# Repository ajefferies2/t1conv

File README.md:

# t1conv

Current Progress: Finished schematics, workinf on layout
100BASE-T1 ↔ 100BASE-TX media converter + dual CAN FD/USB adapter on one
board.

## Features

- Wire-speed T1↔TX conversion, PHY-to-PHY (DP83TC811 ↔ DP83822 over RGMII).
  No MAC, no firmware in the data path, converts with the MCU in reset.
- Two independent CAN FD channels over USB, using the gs_usb protocol:
  works out of the box with SocketCAN, python-can, and SavvyCAN.
- Software-switchable termination on each CAN channel (PhotoMOS; for example,
  `ip link set can0 type can termination 120`).
- Software-selectable T1 master/slave: FET on the strap pin, resampled by
  PHY reset. Boards are identical; role is a console command.
- Powered and flashed over USB-C. Blank MCU enumerates in DFU; BOOT button
  for recovery; SWD pads as last resort.

## Info

- Transformerless T1 MDI: TI-validated CMC, CM termination matched to that
  specific choke, 2 kV coupling network, 100 Ω differential on both MDI sides.
- Back-to-back RGMII delay budget: 25 MHz SDR at 100M, TX+RX internal delay
  strapped in the T1 PHY, strap tables derived from SNLA292/SNLU231.

## Schematics

The images below are exported from the current KiCad hierarchy.

### Top level

### Power

### MCU

### Dual CAN FD

### 100BASE-T1 PHY

### 100BASE-TX Ethernet PHY

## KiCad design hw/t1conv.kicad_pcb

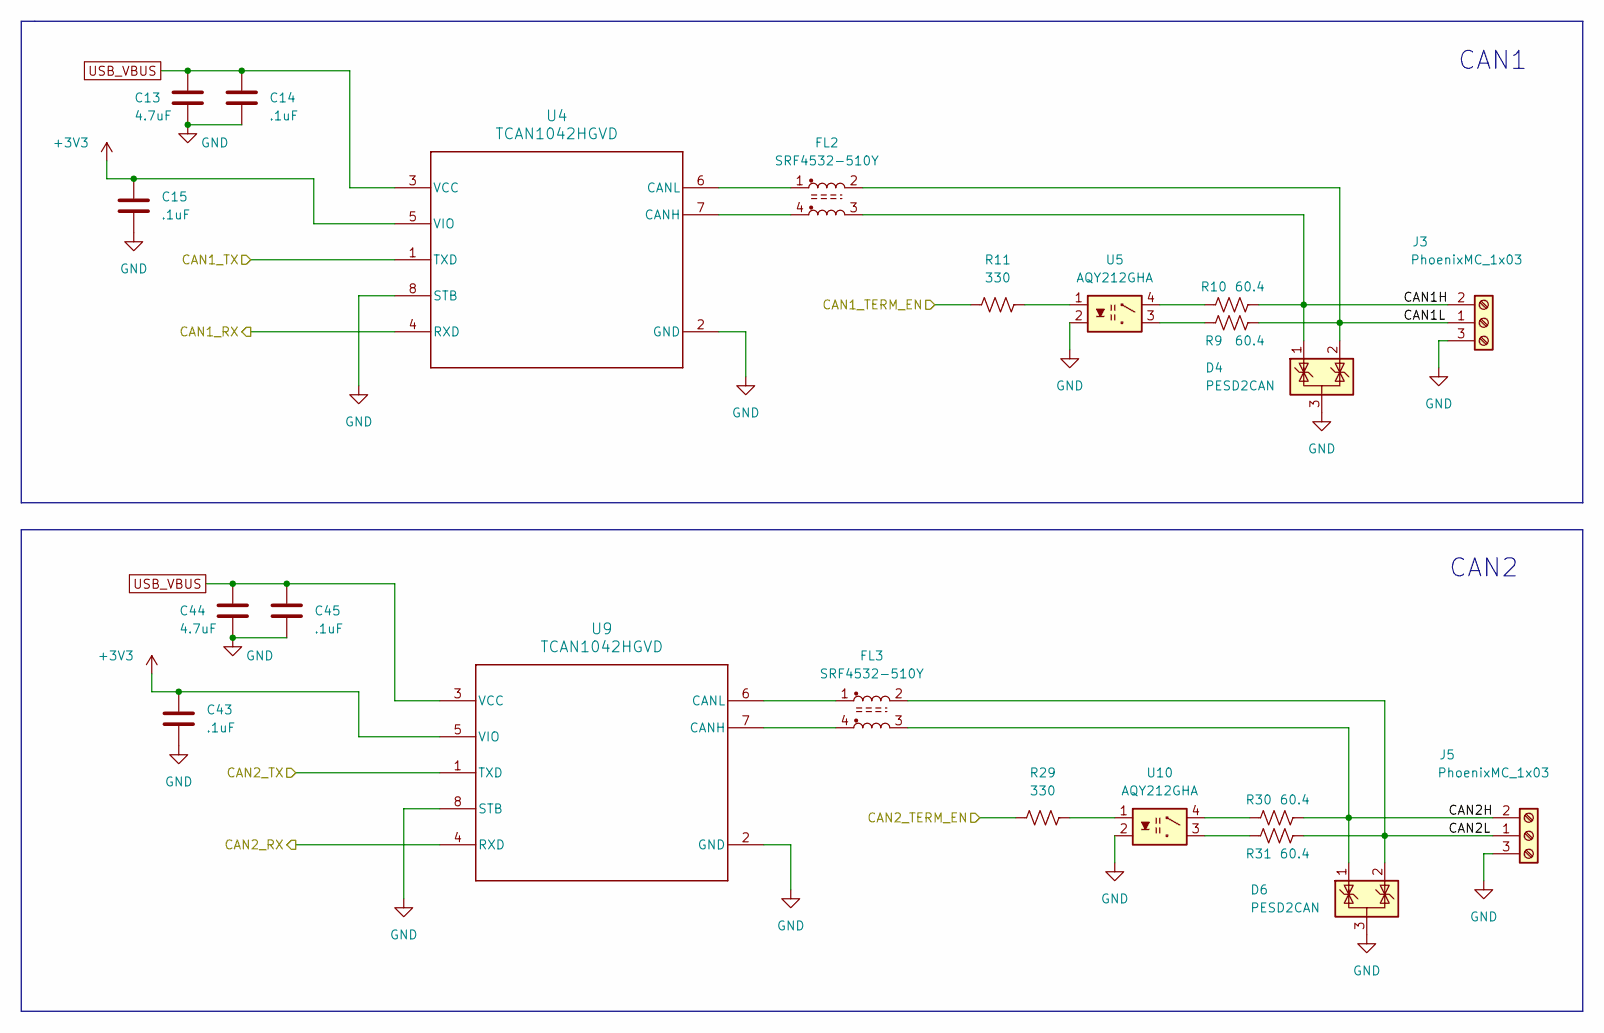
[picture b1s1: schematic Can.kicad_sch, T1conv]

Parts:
C13, C44: 4.7uF; C_0603_1608Metric
C14, C15, C43, C45: .1uF; C_0603_1608Metric
D4, D6: PESD2CAN; SOT-23; MPN PESD2CAN,215; DigiKey 1727-3891-1-ND
FL2, FL3: SRF4532-510Y; SRF4532; MPN SRF4532-510Y; LCSC C2651134
J3, J5: PhoenixMC_1x03; PhoenixContact_MC_1,5_3-G-3.5_1x03_P3.50mm_Horizontal; MPN 1803581
R9, R10, R30, R31: 60.4; R_0603_1608Metric
R11, R29: 330; R_0603_1608Metric
U4, U9: TCAN1042HGVD; TCAN1042_VSON8; MPN TCAN1042HGVD; DigiKey 296-TCAN1042HGVDR-ND
U5, U10: AQY212GHA; MPN AQY212GHAX; DigiKey 255-6063-1-ND

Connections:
+3V3: C15.1, C43.1, U4.5 (VIO), U9.5 (VIO); also elsewhere on the board
/CanSheet/CAN1H: D4.1 (K), FL2.3, J3.2, R10.2
/CanSheet/CAN1L: D4.2 (K), FL2.2, J3.1, R9.2
/CanSheet/CAN1_RX: U4.4 (RXD); also elsewhere on the board
/CanSheet/CAN1_TERM_EN: R11.2; also elsewhere on the board
/CanSheet/CAN1_TX: U4.1 (TXD); also elsewhere on the board
/CanSheet/CAN2H: D6.1 (K), FL3.3, J5.2, R30.2
/CanSheet/CAN2L: D6.2 (K), FL3.2, J5.1, R31.2
/CanSheet/CAN2_RX: U9.4 (RXD); also elsewhere on the board
/CanSheet/CAN2_TERM_EN: R29.2; also elsewhere on the board
/CanSheet/CAN2_TX: U9.1 (TXD); also elsewhere on the board
GND: C13.2, C14.2, C15.2, C43.2, C44.2, C45.2, D4.3 (A), D6.3 (A), J3.3, J5.3, U4.2 (GND), U4.8 (STB), U5.2, U9.2 (GND), U9.8 (STB), U10.2; also elsewhere on the board
unnamed: R9.1, U5.3
unnamed: R10.1, U5.4
unnamed: R11.1, U5.1
unnamed: R29.1, U10.1
unnamed: R30.1, U10.4
unnamed: R31.1, U10.3
unnamed: FL2.4, U4.7 (CANH)
unnamed: FL2.1, U4.6 (CANL)
unnamed: FL3.4, U9.7 (CANH)
unnamed: FL3.1, U9.6 (CANL)
USB_VBUS: C13.1, C14.1, C44.1, C45.1, U4.3 (VCC), U9.3 (VCC); also elsewhere on the board

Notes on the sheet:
CAN2
CAN1

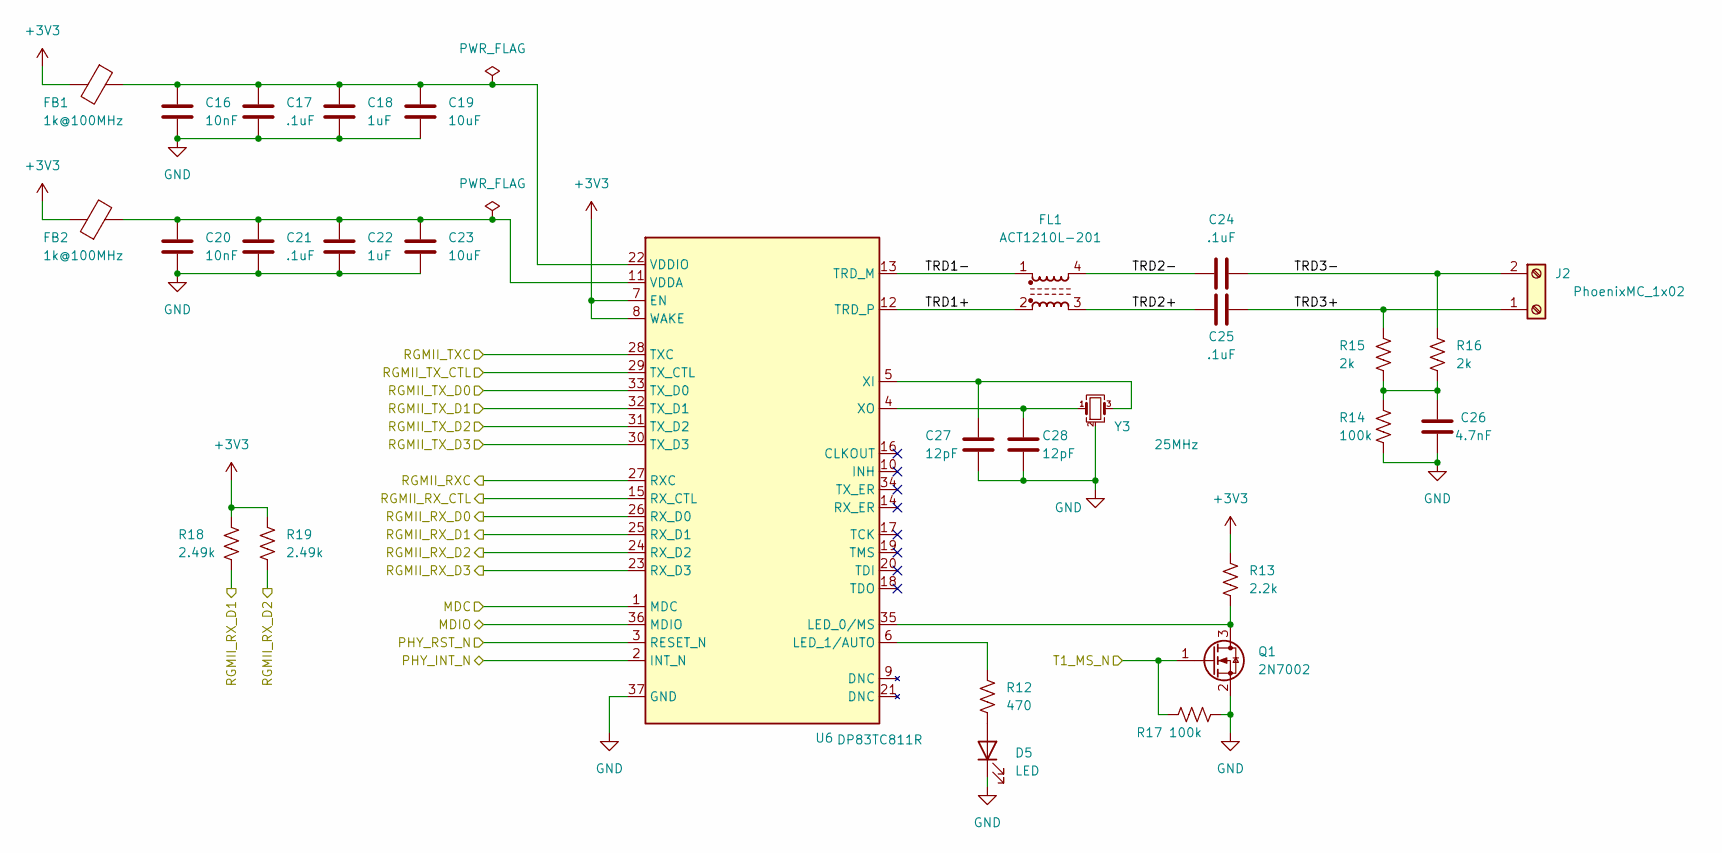
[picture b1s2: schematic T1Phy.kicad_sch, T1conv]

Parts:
C16, C20: 10nF; C_0603_1608Metric
C17, C21, C24, C25: .1uF; C_0603_1608Metric
C18, C22: 1uF; C_0603_1608Metric
C19, C23: 10uF; C_0603_1608Metric
C26: 4.7nF; C_0603_1608Metric
C27, C28: 12pF; C_0603_1608Metric
D5: LED; LED_0603_1608Metric
FB1, FB2: 1k@100MHz; R_0805_2012Metric; MPN house-brand basic tier - pick at sweep 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
FL1: ACT1210L-201; ACT1210L_3225; MPN ACT1210L-201-2P-TL00; DigiKey 445-ACT1210L-201-2P-TL00CT-ND
J2: PhoenixMC_1x02; PhoenixContact_MC_1,5_2-G-3.5_1x02_P3.50mm_Horizontal; MPN 1803578
Q1: 2N7002; SOT-23; MPN 2N7002; LCSC C8545
R12: 470; R_0603_1608Metric
R13: 2.2k; R_0603_1608Metric
R14, R17: 100k; R_0603_1608Metric
R15, R16: 2k; R_0603_1608Metric
R18, R19: 2.49k; R_0603_1608Metric
U6: DP83TC811R; DP83TC811R_RND0036A; MPN DP83TC811RWRNDRQ1; DigiKey 296-DP83TC811RWRNDRQ1-ND
Y3: 25MHz; Crystal_SMD_3225-4Pin_3.2x2.5mm

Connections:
+3V3: FB1.2, FB2.1, R13.1, R18.1, R19.1, U6.7 (EN), U6.8 (WAKE); also elsewhere on the board
/Ethernet/MDC: U6.1 (MDC); also elsewhere on the board
/Ethernet/MDIO: U6.36 (MDIO); also elsewhere on the board
/Ethernet/PHY_INT_N: U6.2 (INT_N); also elsewhere on the board
/Ethernet/PHY_RST_N: U6.3 (RESET_N); also elsewhere on the board
/Ethernet/RGMII_RXC: U6.27 (RXC); also elsewhere on the board
/Ethernet/RGMII_RX_CTL: U6.15 (RX_CTL); also elsewhere on the board
/Ethernet/RGMII_RX_D0: U6.26 (RX_D0); also elsewhere on the board
/Ethernet/RGMII_RX_D1: R18.2, U6.25 (RX_D1); also elsewhere on the board
/Ethernet/RGMII_RX_D2: R19.2, U6.24 (RX_D2); also elsewhere on the board
/Ethernet/RGMII_RX_D3: U6.23 (RX_D3); also elsewhere on the board
/Ethernet/RGMII_TXC: U6.28 (TXC); also elsewhere on the board
/Ethernet/RGMII_TX_CTL: U6.29 (TX_CTL); also elsewhere on the board
/Ethernet/RGMII_TX_D0: U6.33 (TX_D0); also elsewhere on the board
/Ethernet/RGMII_TX_D1: U6.32 (TX_D1); also elsewhere on the board
/Ethernet/RGMII_TX_D2: U6.31 (TX_D2); also elsewhere on the board
/Ethernet/RGMII_TX_D3: U6.30 (TX_D3); also elsewhere on the board
/MCU/T1_MS_N: Q1.1 (G), R17.1; also elsewhere on the board
/T1Phy/TRD1+: FL1.2, U6.12 (TRD_P)
/T1Phy/TRD1-: FL1.1, U6.13 (TRD_M)
/T1Phy/TRD2+: C25.2, FL1.3
/T1Phy/TRD2-: C24.1, FL1.4
/T1Phy/TRD3+: C25.1, J2.1, R15.1
/T1Phy/TRD3-: C24.2, J2.2, R16.1
GND: C16.2, C17.2, C18.2, C19.2, C20.2, C21.2, C22.2, C23.2, C26.2, C27.2, C28.2, D5.1 (K), Q1.2 (S), R14.2, R17.2, U6.37 (GND), Y3.2 (G), Y3.4 (G); also elsewhere on the board
unnamed: C26.1, R14.1, R15.2, R16.2
unnamed: D5.2 (A), R12.2
unnamed: Q1.3 (D), R13.2, U6.35 (LED_0/MS)
unnamed: R12.1, U6.6 (LED_1/AUTO)
unnamed: C20.1, C21.1, C22.1, C23.1, FB2.2, U6.11 (VDDA)
unnamed: C16.1, C17.1, C18.1, C19.1, FB1.1, U6.22 (VDDIO)
unnamed: C27.1, U6.5 (XI), Y3.3
unnamed: C28.1, U6.4 (XO), Y3.1

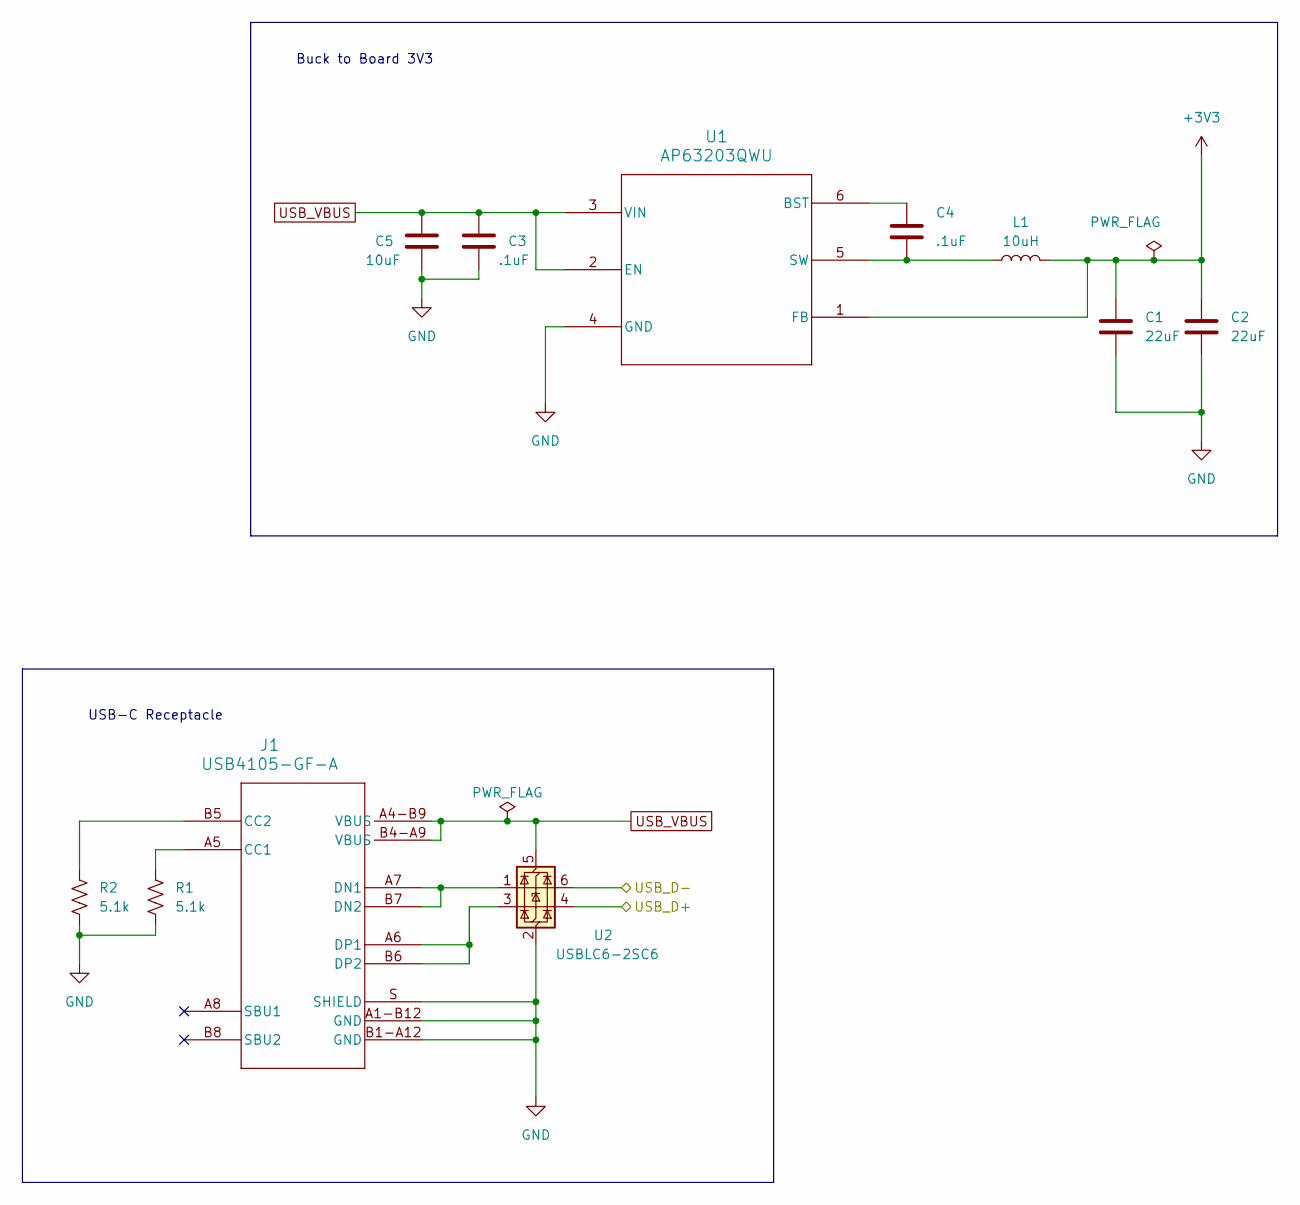
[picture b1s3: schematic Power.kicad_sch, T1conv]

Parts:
C1, C2: 22uF; C_0603_1608Metric
C3, C4: .1uF; C_0603_1608Metric
C5: 10uF; C_0603_1608Metric
J1: USB4105-GF-A; MPN USB4105-GF-A; DigiKey 2073-USB4105-GF-ACT-ND
L1: 10uH; SWPA5040
R1, R2: 5.1k; R_0603_1608Metric
U1: AP63203QWU; AP63203_TSOT26; MPN AP63203QWU-7; DigiKey AP63203QWU-7DICT-ND
U2: USBLC6-2SC6; SOT-23-6; MPN USBLC6-2SC6; DigiKey 497-5235-1-ND

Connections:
+3V3: C1.1, C2.1, L1.2, U1.1 (FB); also elsewhere on the board
/MCU/USB_D+: U2.4 (I/O2); also elsewhere on the board
/MCU/USB_D-: U2.6 (I/O1); also elsewhere on the board
GND: C1.2, C2.2, C3.2, C5.2, J1.A1-B12 (GND), J1.B1-A12 (GND), J1.S (SHIELD), R1.2, R2.2, U1.4 (GND), U2.2 (GND); also elsewhere on the board
unnamed: J1.A5 (CC1), R1.1
unnamed: J1.B5 (CC2), R2.1
unnamed: J1.A7 (DN1), J1.B7 (DN2), U2.1 (I/O1)
unnamed: J1.A6 (DP1), J1.B6 (DP2), U2.3 (I/O2)
unnamed: C4.1, U1.6 (BST)
unnamed: C4.2, L1.1, U1.5 (SW)
USB_VBUS: C3.1, C5.1, J1.A4-B9 (VBUS), J1.B4-A9 (VBUS), U1.2 (EN), U1.3 (VIN), U2.5 (VBUS); also elsewhere on the board

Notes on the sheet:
USB-C Receptacle
Buck to Board 3V3

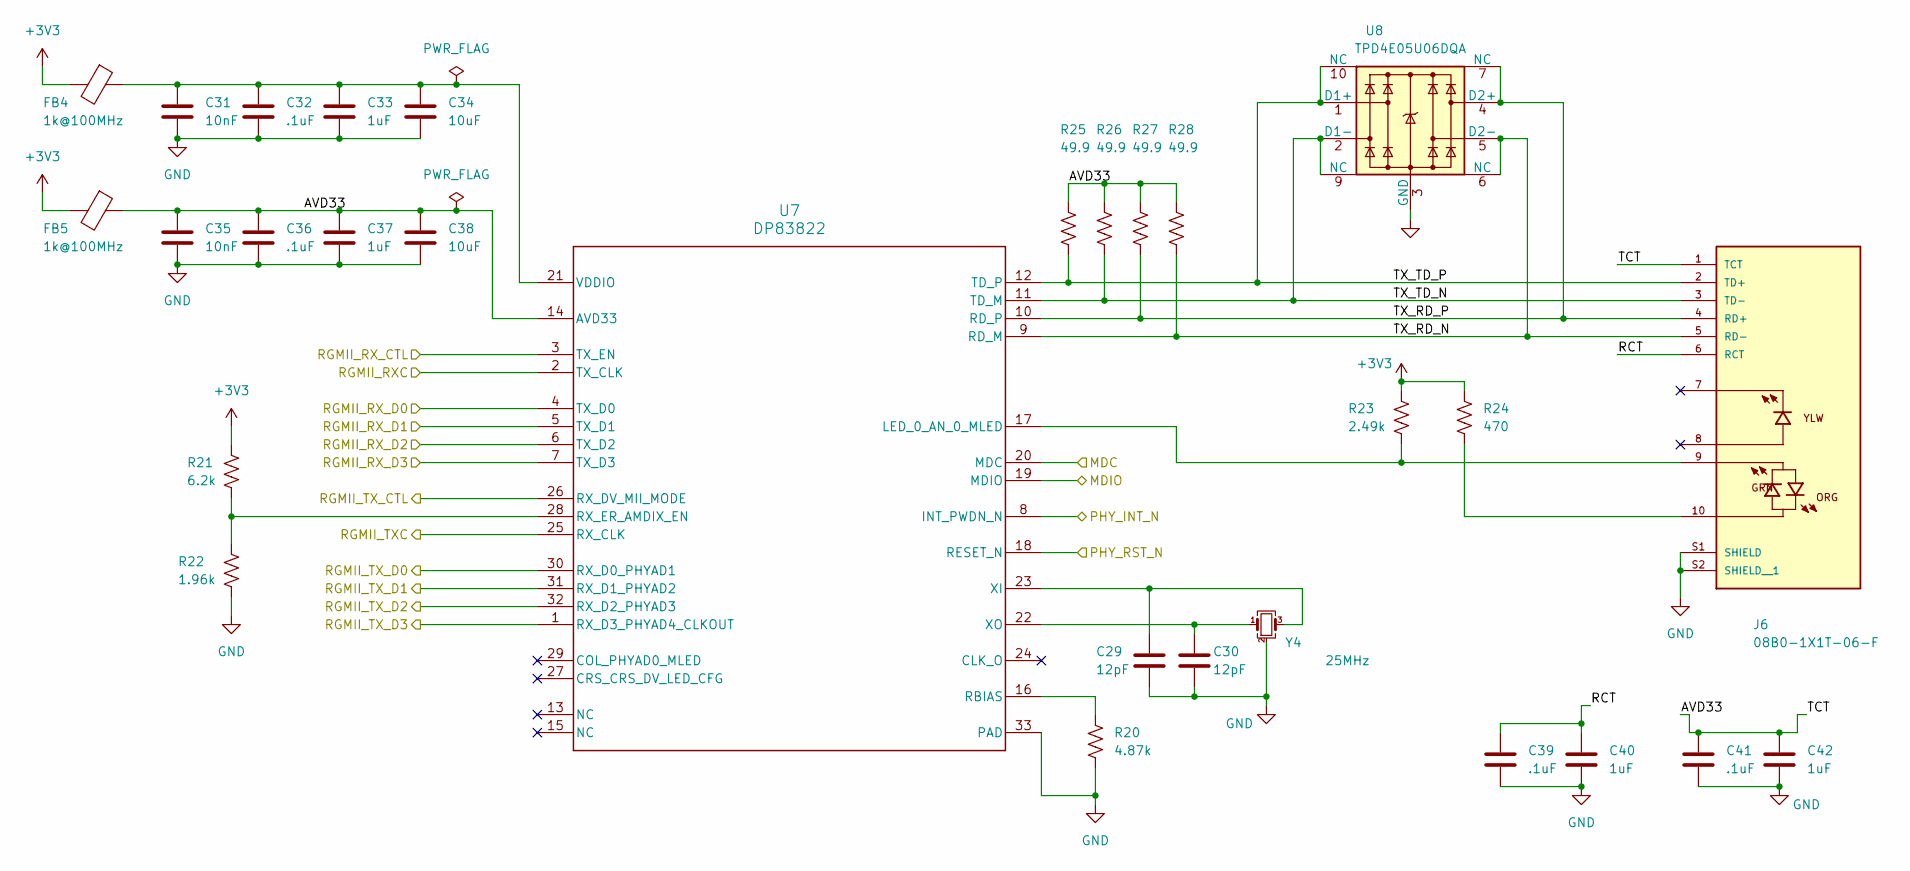
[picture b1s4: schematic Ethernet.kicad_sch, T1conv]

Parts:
C29, C30: 12pF; C_0603_1608Metric
C31, C35: 10nF; C_0603_1608Metric
C32, C36, C39, C41: .1uF; C_0603_1608Metric
C33, C37, C40, C42: 1uF; C_0603_1608Metric
C34, C38: 10uF; C_0603_1608Metric
FB4, FB5: 1k@100MHz; R_0805_2012Metric; MPN house-brand basic tier - pick at sweep 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
J6: 08B0-1X1T-06-F; MPN 08B0-1X1T-06-F; DigiKey 507-1445-ND
R20: 4.87k; R_0603_1608Metric
R21: 6.2k; R_0603_1608Metric
R22: 1.96k; R_0603_1608Metric
R23: 2.49k; R_0603_1608Metric
R24: 470; R_0603_1608Metric
R25, R26, R27, R28: 49.9; R_0603_1608Metric
U7: DP83822; DP83822_RHB0032B; MPN DP83822IRHBR; DigiKey 296-DP83822IRHBRCT-ND
U8: TPD4E05U06DQA; TPD4E05U06_DQA0010A; MPN TPD4E05U06DQAR; DigiKey 296-35765-1-ND
Y4: 25MHz; Crystal_SMD_3225-4Pin_3.2x2.5mm

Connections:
+3V3: FB4.2, FB5.2, R21.1, R23.1, R24.1; also elsewhere on the board
/Ethernet/AVD33: C35.1, C36.1, C37.1, C38.1, C41.1, C42.1, FB5.1, J6.1 (TCT), R25.1, R26.1, R27.1, R28.1, U7.14 (AVD33)
/Ethernet/MDC: U7.20 (MDC); also elsewhere on the board
/Ethernet/MDIO: U7.19 (MDIO); also elsewhere on the board
/Ethernet/PHY_INT_N: U7.8 (INT_PWDN_N); also elsewhere on the board
/Ethernet/PHY_RST_N: U7.18 (RESET_N); also elsewhere on the board
/Ethernet/RCT: C39.1, C40.1, J6.6 (RCT)
/Ethernet/RGMII_RXC: U7.2 (TX_CLK); also elsewhere on the board
/Ethernet/RGMII_RX_CTL: U7.3 (TX_EN); also elsewhere on the board
/Ethernet/RGMII_RX_D0: U7.4 (TX_D0); also elsewhere on the board
/Ethernet/RGMII_RX_D1: U7.5 (TX_D1); also elsewhere on the board
/Ethernet/RGMII_RX_D2: U7.6 (TX_D2); also elsewhere on the board
/Ethernet/RGMII_RX_D3: U7.7 (TX_D3); also elsewhere on the board
/Ethernet/RGMII_TXC: U7.25 (RX_CLK); also elsewhere on the board
/Ethernet/RGMII_TX_CTL: U7.26 (RX_DV_MII_MODE); also elsewhere on the board
/Ethernet/RGMII_TX_D0: U7.30 (RX_D0_PHYAD1); also elsewhere on the board
/Ethernet/RGMII_TX_D1: U7.31 (RX_D1_PHYAD2); also elsewhere on the board
/Ethernet/RGMII_TX_D2: U7.32 (RX_D2_PHYAD3); also elsewhere on the board
/Ethernet/RGMII_TX_D3: U7.1 (RX_D3_PHYAD4_CLKOUT); also elsewhere on the board
/Ethernet/TX_RD_N: J6.5 (RD-), R28.2, U7.9 (RD_M), U8.5 (D2-), U8.6 (NC)
/Ethernet/TX_RD_P: J6.4 (RD+), R27.2, U7.10 (RD_P), U8.4 (D2+), U8.7 (NC)
/Ethernet/TX_TD_N: J6.3 (TD-), R26.2, U7.11 (TD_M), U8.2 (D1-), U8.9 (NC)
/Ethernet/TX_TD_P: J6.2 (TD+), R25.2, U7.12 (TD_P), U8.1 (D1+), U8.10 (NC)
GND: C29.2, C30.2, C31.2, C32.2, C33.2, C34.2, C35.2, C36.2, C37.2, C38.2, C39.2, C40.2, C41.2, C42.2, J6.S1 (SHIELD), J6.S2 (SHIELD__1), R20.2, R22.2, U7.33 (PAD), U8.3 (GND), U8.8 (GND), Y4.2 (G), Y4.4 (G); also elsewhere on the board
unnamed: J6.10, R24.2
unnamed: J6.9, R23.2, U7.17 (LED_0_AN_0_MLED)
unnamed: R20.1, U7.16 (RBIAS)
unnamed: R21.2, R22.1, U7.28 (RX_ER_AMDIX_EN)
unnamed: C31.1, C32.1, C33.1, C34.1, FB4.1, U7.21 (VDDIO)
unnamed: C29.1, U7.23 (XI), Y4.3
unnamed: C30.1, U7.22 (XO), Y4.1

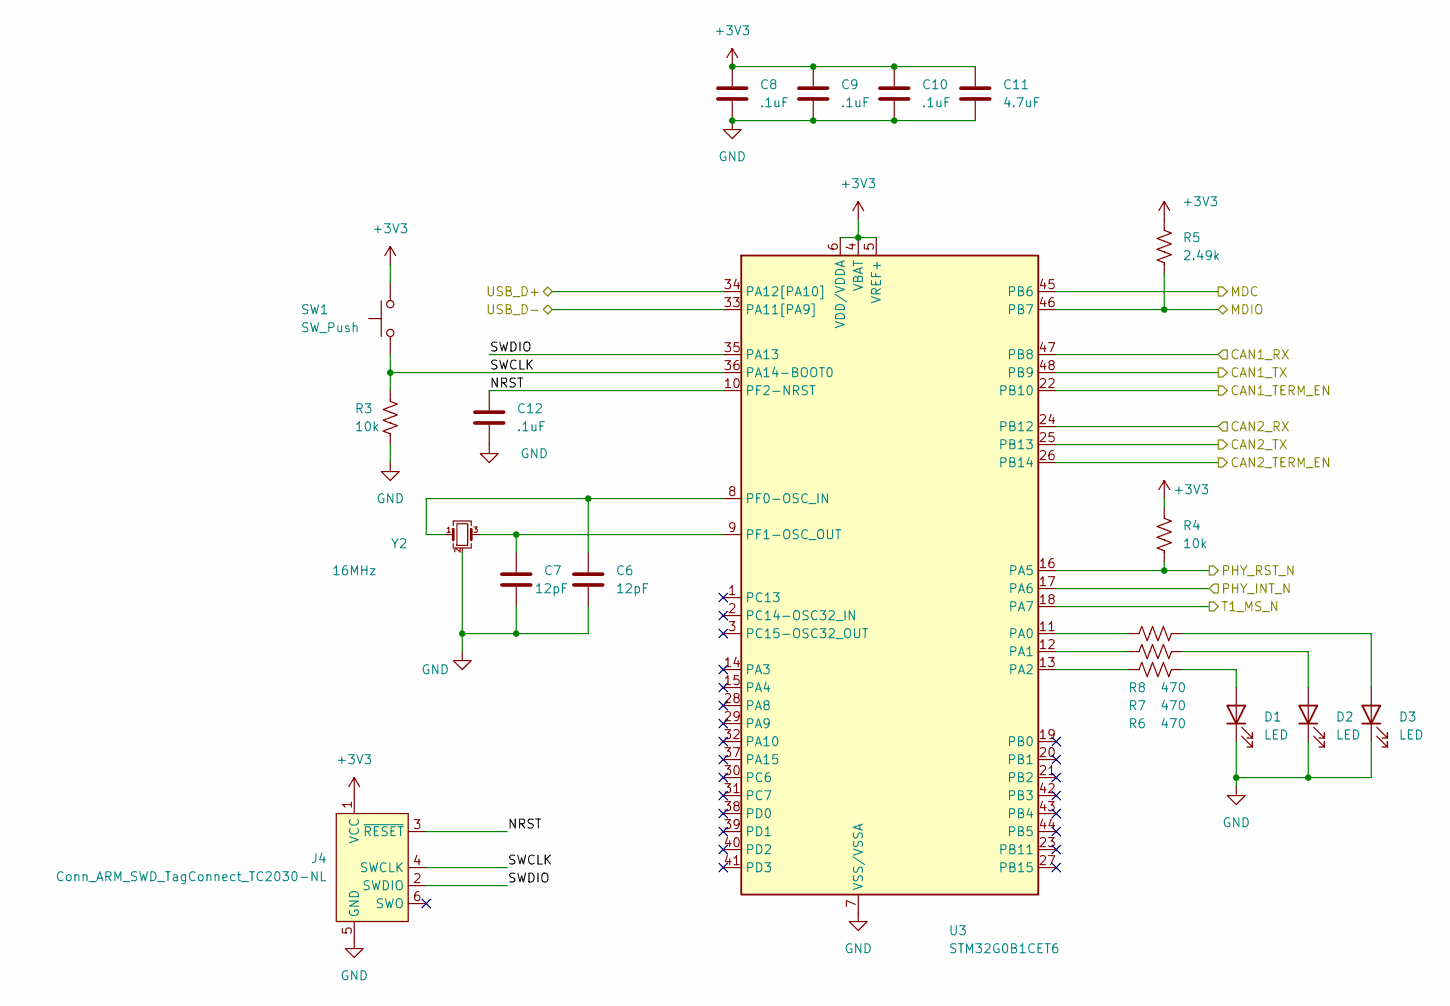
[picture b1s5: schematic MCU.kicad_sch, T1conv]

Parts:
C6, C7: 12pF; C_0603_1608Metric
C8, C9, C10, C12: .1uF; C_0603_1608Metric
C11: 4.7uF; C_0603_1608Metric
D1, D2, D3: LED; LED_0603_1608Metric
J4: Conn_ARM_SWD_TagConnect_TC2030-NL; Tag-Connect_TC2030-IDC-NL_2x03_P1.27mm_Vertical
R3, R4: 10k; R_0603_1608Metric
R5: 2.49k; R_0603_1608Metric
R6, R7, R8: 470; R_0603_1608Metric
SW1: SW_Push; SW_Push_Panasonic_EVQP4_EdgeMount
U3: STM32G0B1CET6; STM32G0B1_LQFP48; MPN STM32G0B1CET6; DigiKey 497-STM32G0B1CET6-ND
Y2: 16MHz; Crystal_SMD_3225-4Pin_3.2x2.5mm

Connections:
+3V3: C8.1, C9.1, C10.1, C11.1, J4.1 (VCC), R4.1, R5.1, SW1.2, U3.4 (VBAT), U3.5 (VREF+), U3.6 (VDD/VDDA); also elsewhere on the board
/CanSheet/CAN1_RX: U3.47 (PB8); also elsewhere on the board
/CanSheet/CAN1_TERM_EN: U3.22 (PB10); also elsewhere on the board
/CanSheet/CAN1_TX: U3.48 (PB9); also elsewhere on the board
/CanSheet/CAN2_RX: U3.24 (PB12); also elsewhere on the board
/CanSheet/CAN2_TERM_EN: U3.26 (PB14); also elsewhere on the board
/CanSheet/CAN2_TX: U3.25 (PB13); also elsewhere on the board
/Ethernet/MDC: U3.45 (PB6); also elsewhere on the board
/Ethernet/MDIO: R5.2, U3.46 (PB7); also elsewhere on the board
/Ethernet/PHY_INT_N: U3.17 (PA6); also elsewhere on the board
/Ethernet/PHY_RST_N: R4.2, U3.16 (PA5); also elsewhere on the board
/MCU/NRST: C12.1, J4.3 (~RESET), U3.10 (PF2-NRST)
/MCU/SWCLK: J4.4 (SWCLK), R3.1, SW1.1, U3.36 (PA14-BOOT0)
/MCU/SWDIO: J4.2 (SWDIO), U3.35 (PA13)
/MCU/T1_MS_N: U3.18 (PA7); also elsewhere on the board
/MCU/USB_D+: U3.34 (PA12[PA10]); also elsewhere on the board
/MCU/USB_D-: U3.33 (PA11[PA9]); also elsewhere on the board
GND: C6.2, C7.2, C8.2, C9.2, C10.2, C11.2, C12.2, D1.1 (K), D2.1 (K), D3.1 (K), J4.5 (GND), R3.2, U3.7 (VSS/VSSA), Y2.2 (G), Y2.4 (G); also elsewhere on the board
unnamed: D1.2 (A), R6.2
unnamed: D2.2 (A), R7.2
unnamed: D3.2 (A), R8.2
unnamed: R8.1, U3.11 (PA0)
unnamed: R7.1, U3.12 (PA1)
unnamed: R6.1, U3.13 (PA2)
unnamed: C6.1, U3.8 (PF0-OSC_IN), Y2.1
unnamed: C7.1, U3.9 (PF1-OSC_OUT), Y2.3

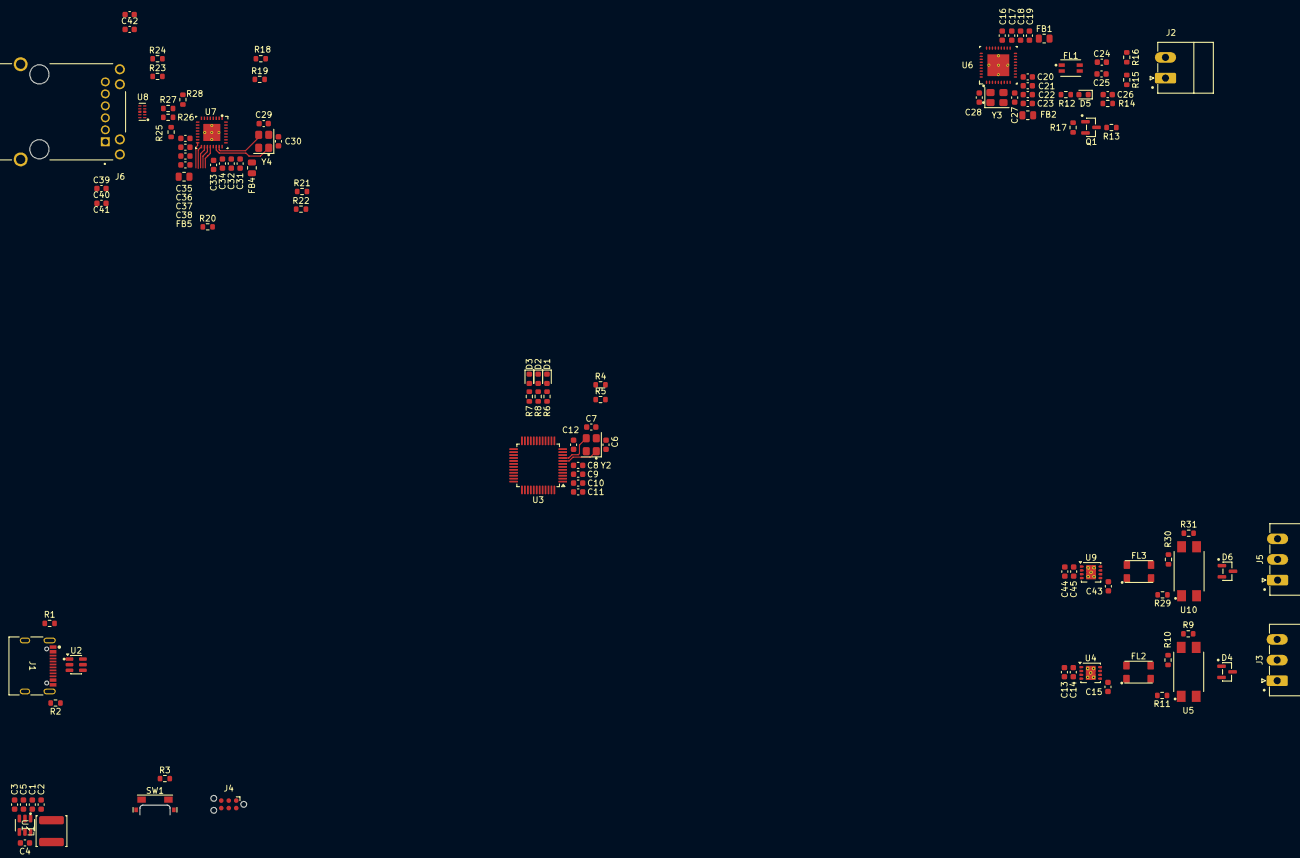
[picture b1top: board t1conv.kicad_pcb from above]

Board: 4 copper layers, 111 parts (0 on the bottom side), 86 nets.
